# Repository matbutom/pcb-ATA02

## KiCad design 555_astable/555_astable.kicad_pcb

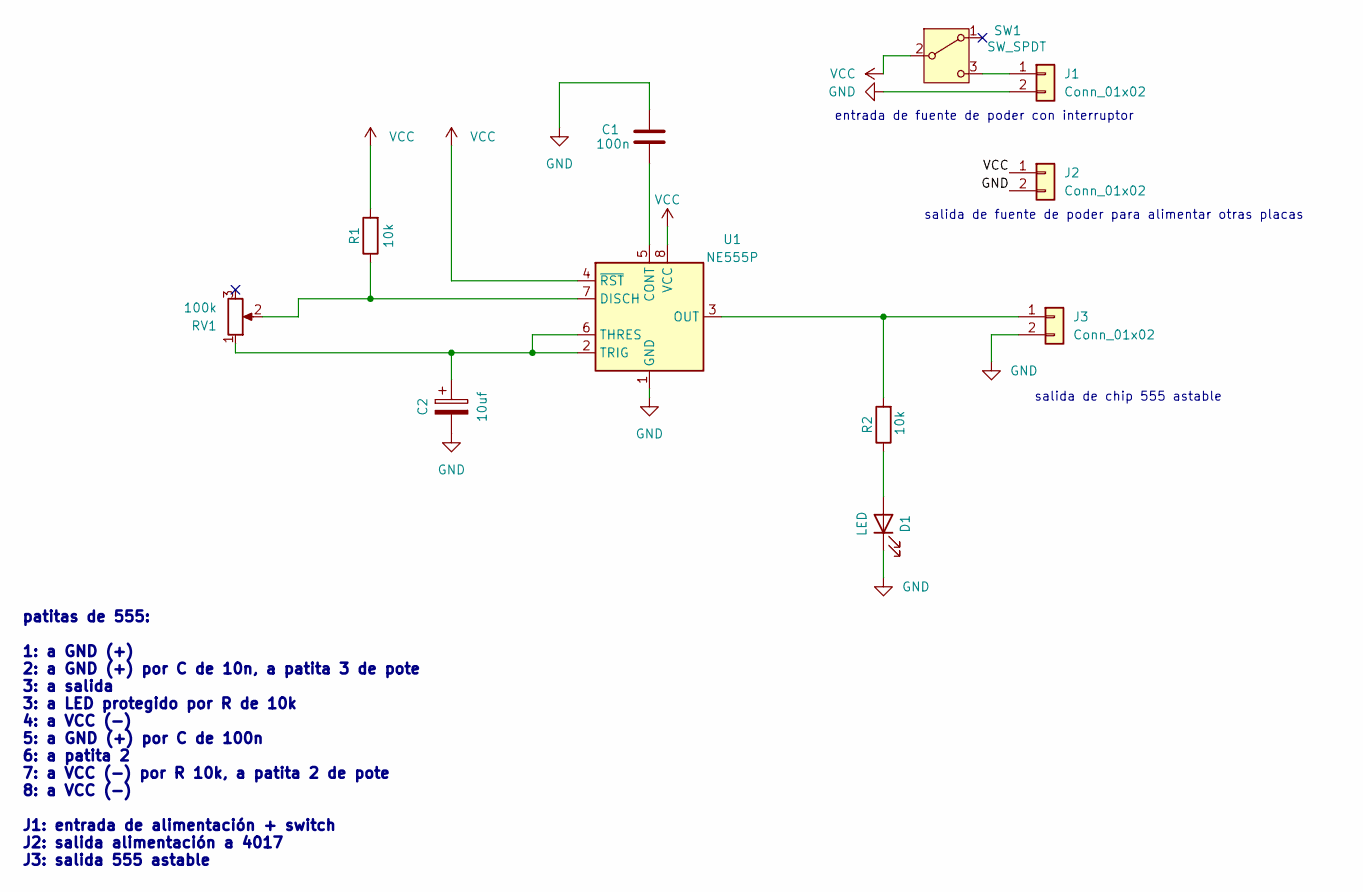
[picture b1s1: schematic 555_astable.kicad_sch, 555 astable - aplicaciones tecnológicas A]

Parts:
C1: 100n; C_Disc_D5.0mm_W2.5mm_P5.00mm
C2: 10uf; CP_Radial_D5.0mm_P2.50mm
D1: LED; LED_D5.0mm
J1, J2, J3: Conn_01x02; TerminalBlock_MaiXu_MX126-5.0-02P_1x02_P5.00mm
R1, R2: 10k; R_Axial_DIN0207_L6.3mm_D2.5mm_P10.16mm_Horizontal
RV1: 100k; TerminalBlock_MaiXu_MX126-5.0-02P_1x02_P5.00mm
SW1: SW_SPDT; spdt_ssd12d00g3
U1: NE555P; DIP-8_W7.62mm_Socket

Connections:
GND: C1.1, C2.2, D1.1 (K), J1.2, J2.2, J3.2, U1.1 (GND)
unnamed: D1.2 (A), R2.1
unnamed: J1.1, SW1.3 (C)
unnamed: J3.1, R2.2, U1.3 (OUT)
unnamed: C1.2, U1.5 (CONT)
unnamed: R1.1, RV1.2, U1.7 (DISCH)
unnamed: C2.1, RV1.1, U1.2 (TRIG), U1.6 (THRES)
VCC: J2.1, R1.2, SW1.2 (B), U1.4 (~RST), U1.8 (VCC)

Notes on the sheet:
salida de fuente de poder para alimentar otras placas
salida de chip 555 astable
patitas de 555: 1: a GND (+) 2: a GND (+) por C de 10n, a patita 3 de pote 3: a salida 3: a LED protegido por R de 10k 4: a VCC (-) 5: a GND (+) por C de 100n 6: a patita 2 7: a VCC (-) por R 10k, a patita 2 de pote 8: a VCC (-) J1: entrada de alimentación + switch J2: salida alimentación a 4017 J3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
entrada de fuente de poder con interruptor

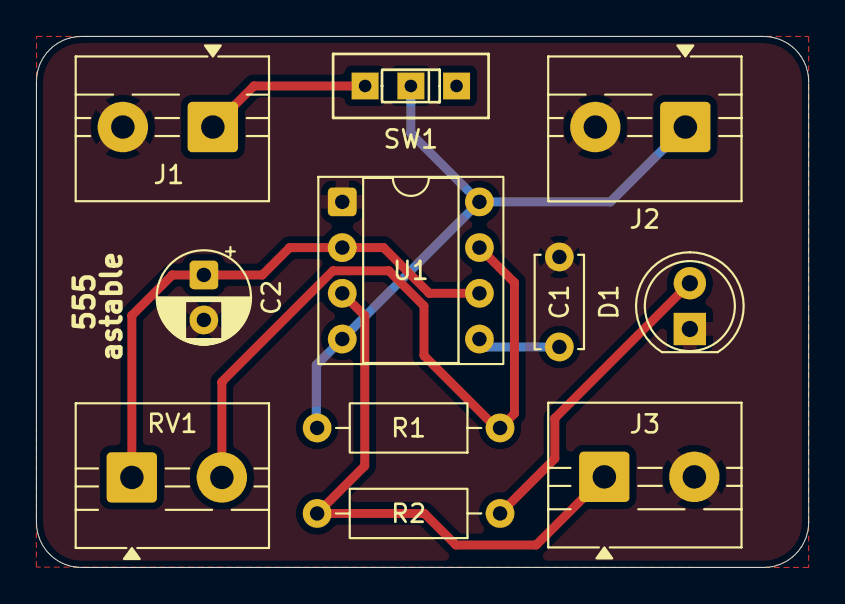
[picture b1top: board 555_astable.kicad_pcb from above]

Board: 2 copper layers, 42.9 x 29.5 mm, 11 parts (0 on the bottom side), 8 nets.

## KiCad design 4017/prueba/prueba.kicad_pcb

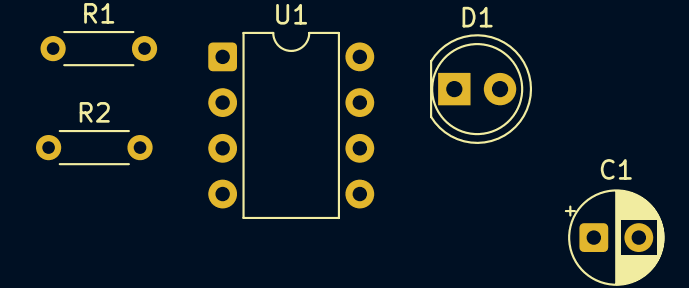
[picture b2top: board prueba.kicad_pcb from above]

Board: 2 copper layers, 5 parts (0 on the bottom side), 7 nets, no tracks yet.

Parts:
C1: C_Polarized; CP_Radial_D5.0mm_P2.50mm
D1: LED; LED_D5.0mm
R1: 10k; R_Axial_DIN0204_L3.6mm_D1.6mm_P5.08mm_Horizontal
R2: R; R_Axial_DIN0204_L3.6mm_D1.6mm_P5.08mm_Horizontal
U1: NA555P; DIP-8_W7.62mm

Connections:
GND: C1.2, D1.1 (K), U1.1 (GND)
unnamed: D1.2 (A), R2.2
unnamed: C1.1, U1.5 (CONT)
unnamed: R1.2, U1.7 (DISCH)
unnamed: R2.1, U1.3 (OUT)
unnamed: U1.2 (TRIG), U1.6 (THRES)
VCC: R1.1, U1.4 (~RST), U1.8 (VCC)

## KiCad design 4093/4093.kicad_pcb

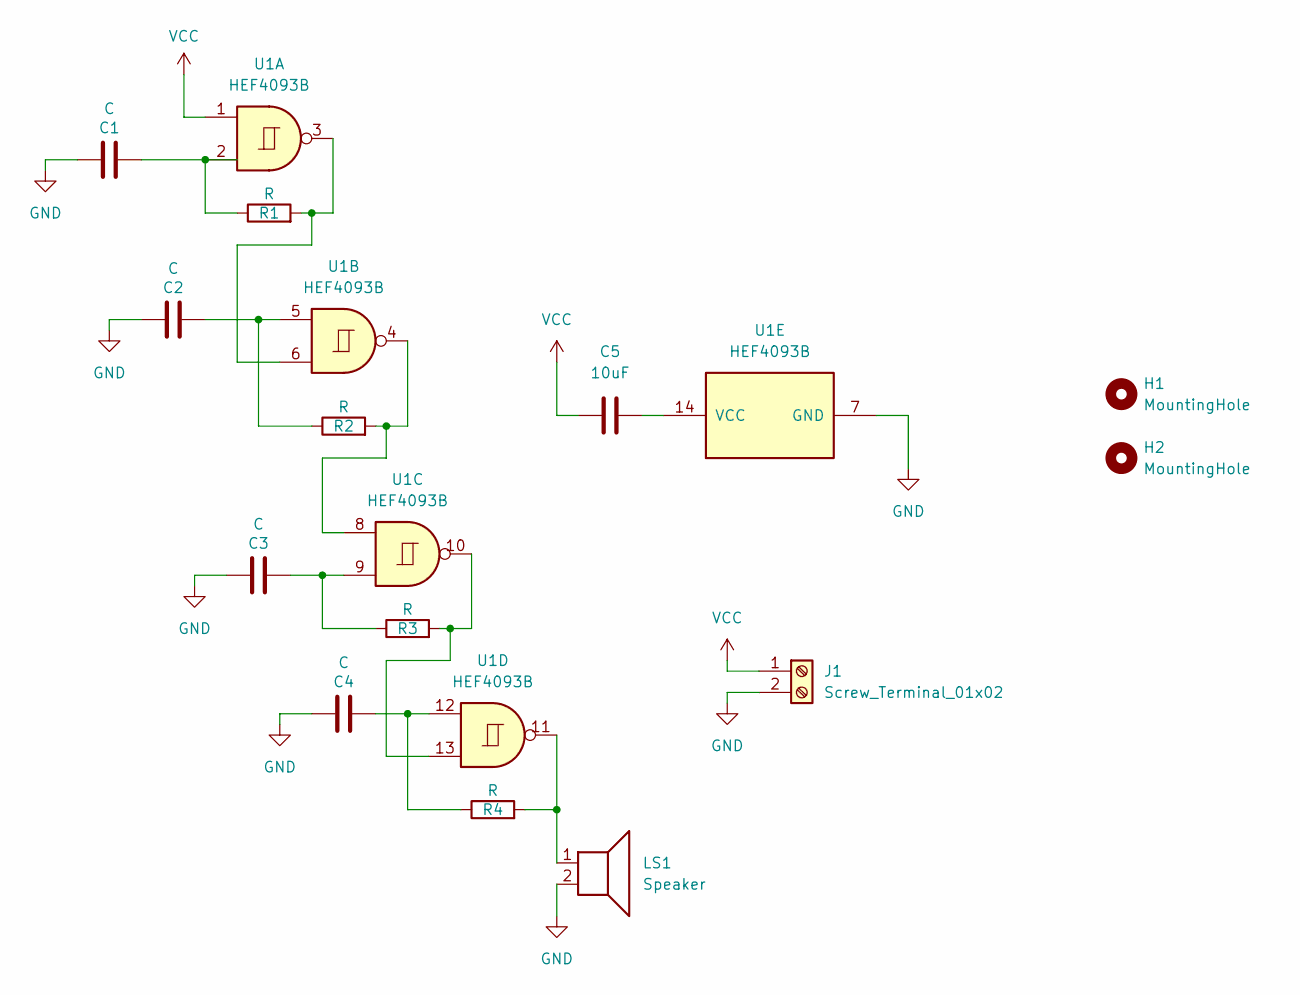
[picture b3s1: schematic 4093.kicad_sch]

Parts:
C1, C2, C3, C4: C; CP_Radial_D5.0mm_P2.00mm
C5: 10uF; CP_Radial_D5.0mm_P2.00mm
H1, H2: MountingHole; MountingHole_3.2mm_M3
J1: Screw_Terminal_01x02; TerminalBlock_MaiXu_MX126-5.0-02P_1x02_P5.00mm
LS1: Speaker; TerminalBlock_MaiXu_MX126-5.0-02P_1x02_P5.00mm
R1, R2, R3, R4: R; TerminalBlock_MaiXu_MX126-5.0-02P_1x02_P5.00mm
U1: HEF4093B; DIP-14_W7.62mm_Socket

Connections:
GND: C1.1, C2.1, C3.1, C4.1, J1.2, LS1.2, U1.7 (GND)
unnamed: C1.2, R1.1, U1.2
unnamed: C2.2, R2.1, U1.5
unnamed: C3.2, R3.1, U1.9
unnamed: C4.2, R4.1, U1.12
unnamed: LS1.1, R4.2, U1.11
unnamed: R1.2, U1.3, U1.6
unnamed: R2.2, U1.4, U1.8
unnamed: R3.2, U1.10, U1.13
unnamed: C5.2, U1.14 (VCC)
VCC: C5.1, J1.1, U1.1

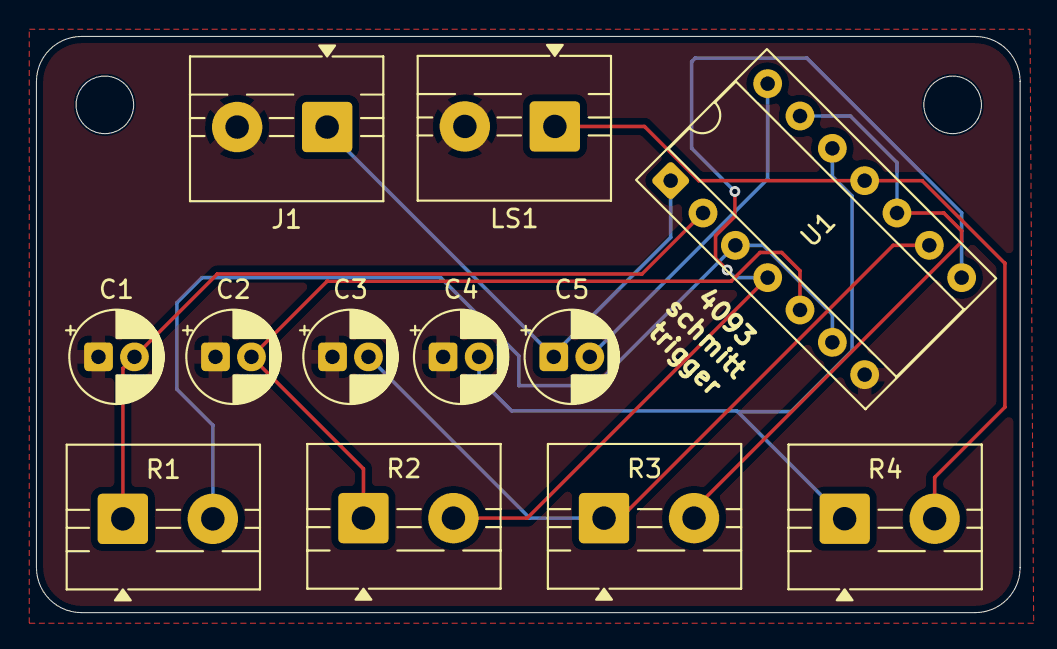
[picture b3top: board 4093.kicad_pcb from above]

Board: 2 copper layers, 54.7 x 32.0 mm, 14 parts (0 on the bottom side), 11 nets.

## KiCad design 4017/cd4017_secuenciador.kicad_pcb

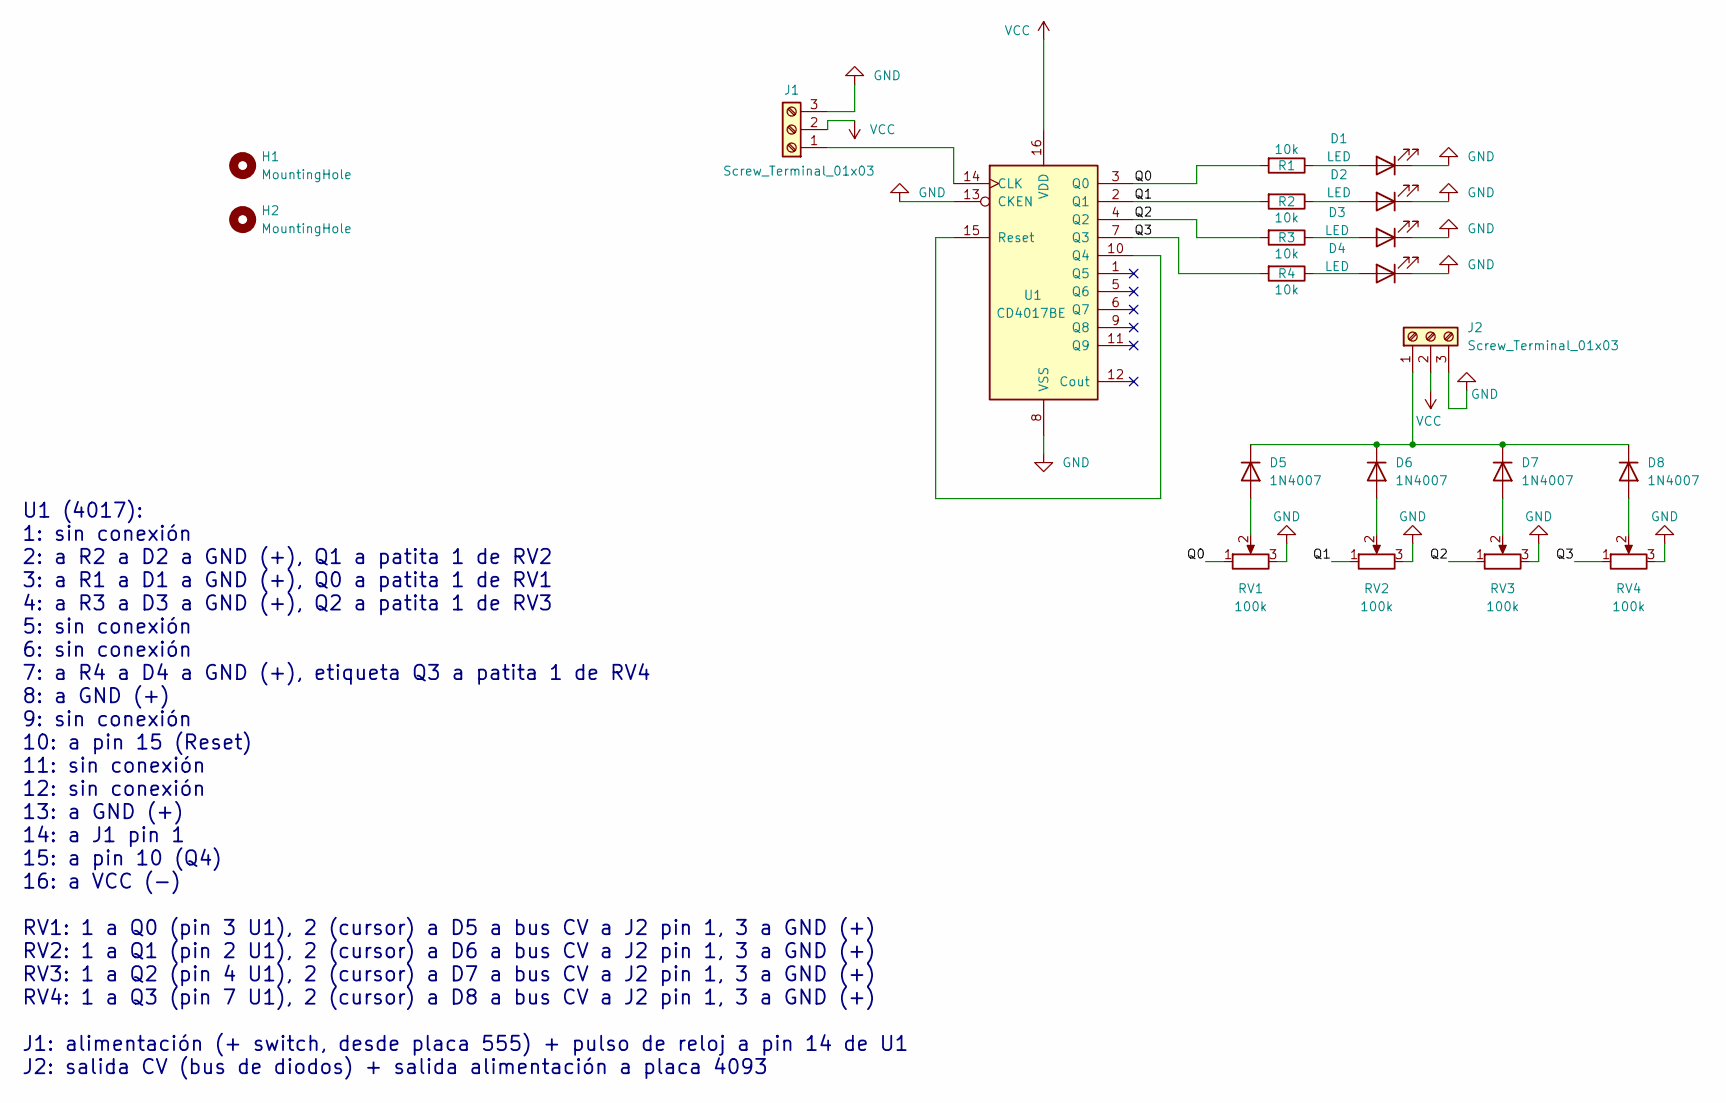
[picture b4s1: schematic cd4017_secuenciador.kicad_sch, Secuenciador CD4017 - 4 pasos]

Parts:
D1, D2, D3, D4: LED; LED_D5.0mm
D5, D6, D7, D8: 1N4007; D_DO-41_SOD81_P10.16mm_Horizontal
H1, H2: MountingHole
J1, J2: Screw_Terminal_01x03; TerminalBlock_MaiXu_MX126-5.0-03P_1x03_P5.00mm
R1, R2, R3, R4: 10k; R_Axial_DIN0207_L6.3mm_D2.5mm_P10.16mm_Horizontal
RV1, RV2, RV3, RV4: 100k; TerminalBlock_MaiXu_MX126-5.0-03P_1x03_P5.00mm
U1: CD4017BE; DIP-16_W7.62mm_Socket

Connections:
/Q0: R1.2, RV1.1, U1.3 (Q0)
/Q1: R2.2, RV2.1, U1.2 (Q1)
/Q2: R3.2, RV3.1, U1.4 (Q2)
/Q3: R4.2, RV4.1, U1.7 (Q3)
GND: D1.1 (K), D2.1 (K), D3.1 (K), D4.1 (K), J1.3, J2.3, RV1.3, RV2.3, RV3.3, RV4.3, U1.8 (VSS), U1.13 (CKEN)
unnamed: D1.2 (A), R1.1
unnamed: D2.2 (A), R2.1
unnamed: D3.2 (A), R3.1
unnamed: D4.2 (A), R4.1
unnamed: D5.2 (A), RV1.2
unnamed: D5.1 (K), D6.1 (K), D7.1 (K), D8.1 (K), J2.1
unnamed: D6.2 (A), RV2.2
unnamed: D7.2 (A), RV3.2
unnamed: D8.2 (A), RV4.2
unnamed: J1.1, U1.14 (CLK)
unnamed: U1.10 (Q4), U1.15 (Reset)
VCC: J1.2, J2.2, U1.16 (VDD)

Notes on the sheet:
U1 (4017): 1: sin conexión 2: a R2 a D2 a GND (+), Q1 a patita 1 de RV2 3: a R1 a D1 a GND (+), Q0 a patita 1 de RV1 4: a R3 a D3 a GND (+), Q2 a patita 1 de RV3 5: sin conexión 6: sin conexión 7: a R4 a D4 a GND (+), etiqueta Q3 a patita 1 de RV4 8: a GND (+) 9: sin conexión 10: a pin 15 (Reset) 1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

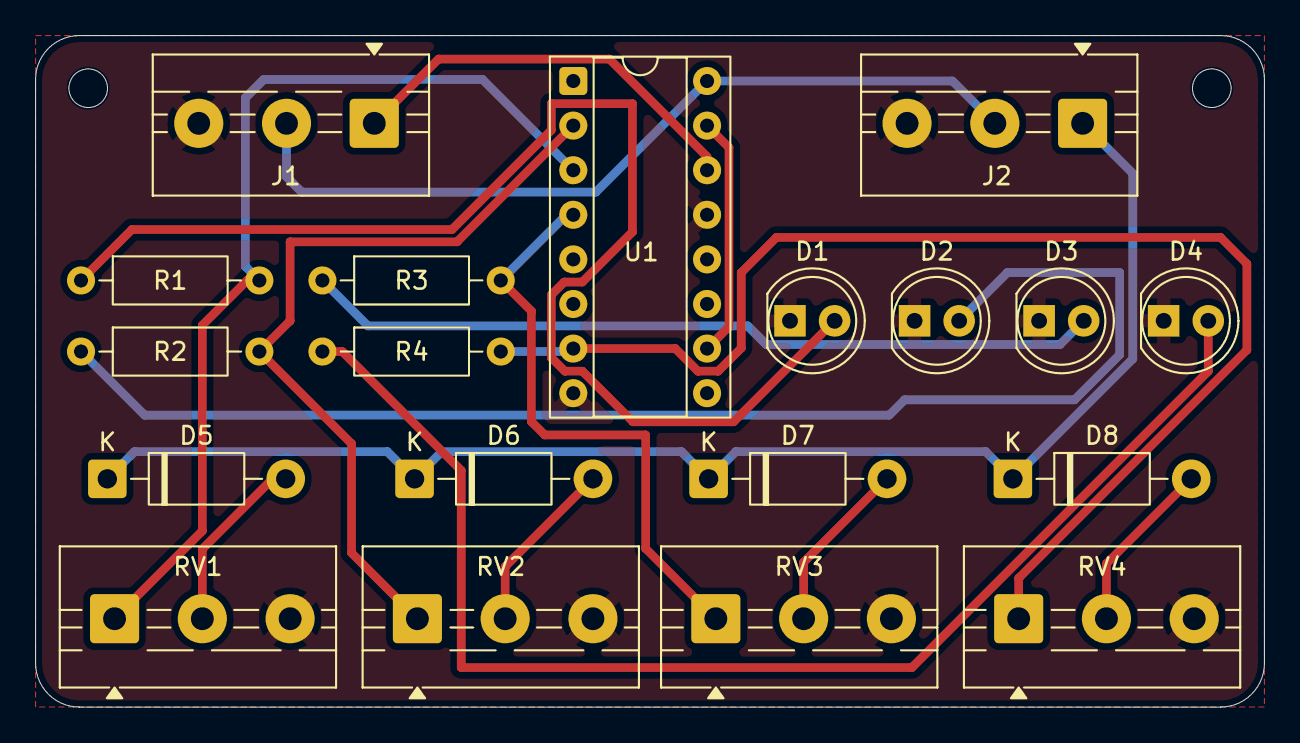
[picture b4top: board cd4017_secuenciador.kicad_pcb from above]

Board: 2 copper layers, 70.0 x 38.2 mm, 19 parts (0 on the bottom side), 17 nets.

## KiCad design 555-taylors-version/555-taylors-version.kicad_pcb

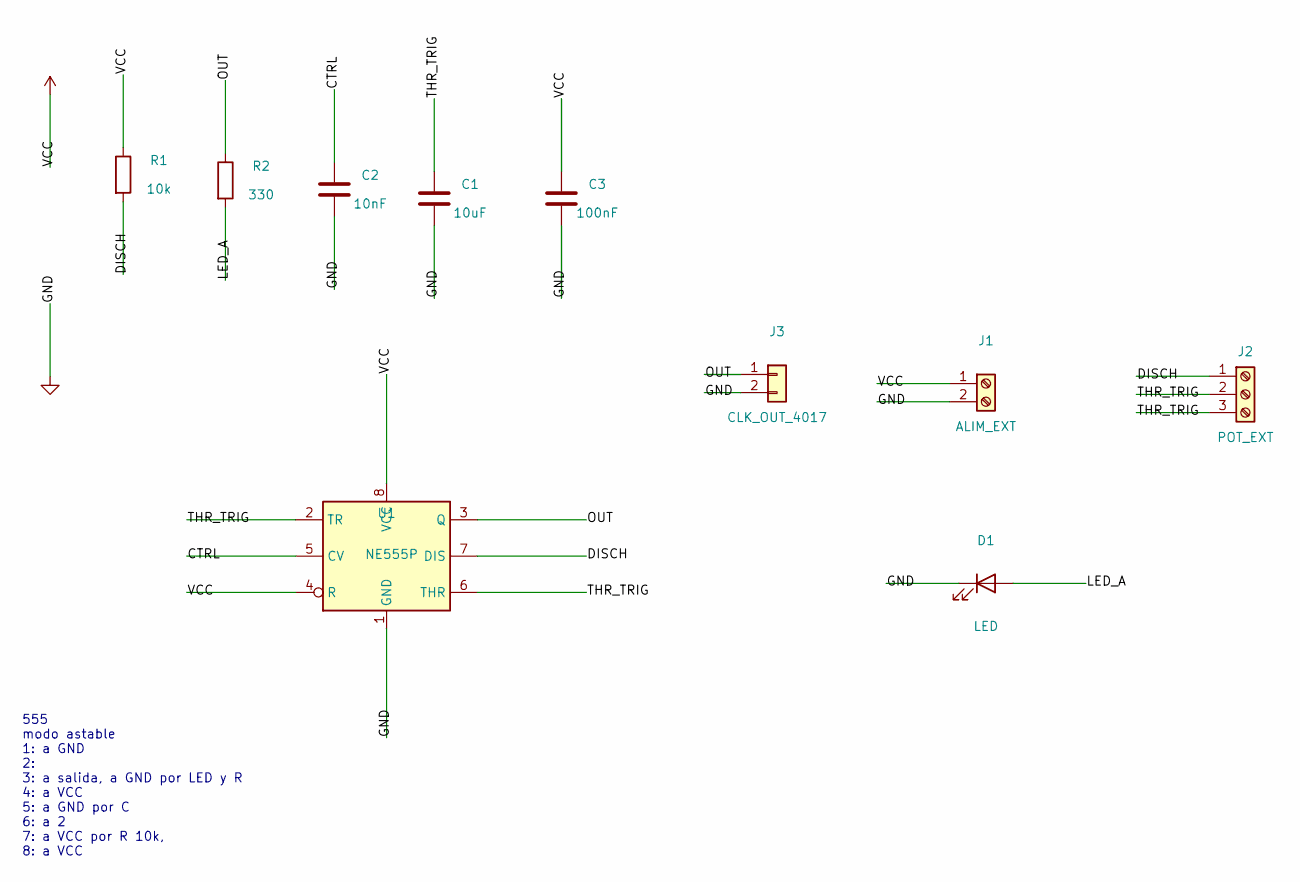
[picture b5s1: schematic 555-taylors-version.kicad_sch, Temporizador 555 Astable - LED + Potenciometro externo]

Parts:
C1: 10uF; CP_Radial_D5.0mm_P2.50mm
C2: 10nF; C_Disc_D3.0mm_W1.6mm_P2.50mm
C3: 100nF; C_Disc_D3.0mm_W1.6mm_P2.50mm
D1: LED; LED_D5.0mm
J1: ALIM_EXT; TerminalBlock_bornier-2_P5.08mm
J2: POT_EXT; TerminalBlock_bornier-3_P5.08mm
J3: CLK_OUT_4017; PinHeader_1x02_P2.54mm_Vertical
R1: 10k; R_Axial_DIN0207_L6.3mm_D2.5mm_P10.16mm_Horizontal
R2: 330; R_Axial_DIN0207_L6.3mm_D2.5mm_P10.16mm_Horizontal
U1: NE555P; DIP-8_W7.62mm_Socket

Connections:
CTRL: C2.1, U1.5 (CV)
DISCH: J2.1, R1.2, U1.7 (DIS)
GND: C1.2, C2.2, C3.2, D1.1 (K), J1.2, J3.2, U1.1 (GND)
LED_A: D1.2 (A), R2.2
OUT: J3.1, R2.1, U1.3 (Q)
THR_TRIG: C1.1, J2.2, J2.3, U1.2 (TR), U1.6 (THR)
VCC: C3.1, J1.1, R1.1, U1.4 (R), U1.8 (VCC)

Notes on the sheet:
555 modo astable 1: a GND 2: 3: a salida, a GND por LED y R 4: a VCC 5: a GND por C 6: a 2 7: a VCC por R 10k, 8: a VCC

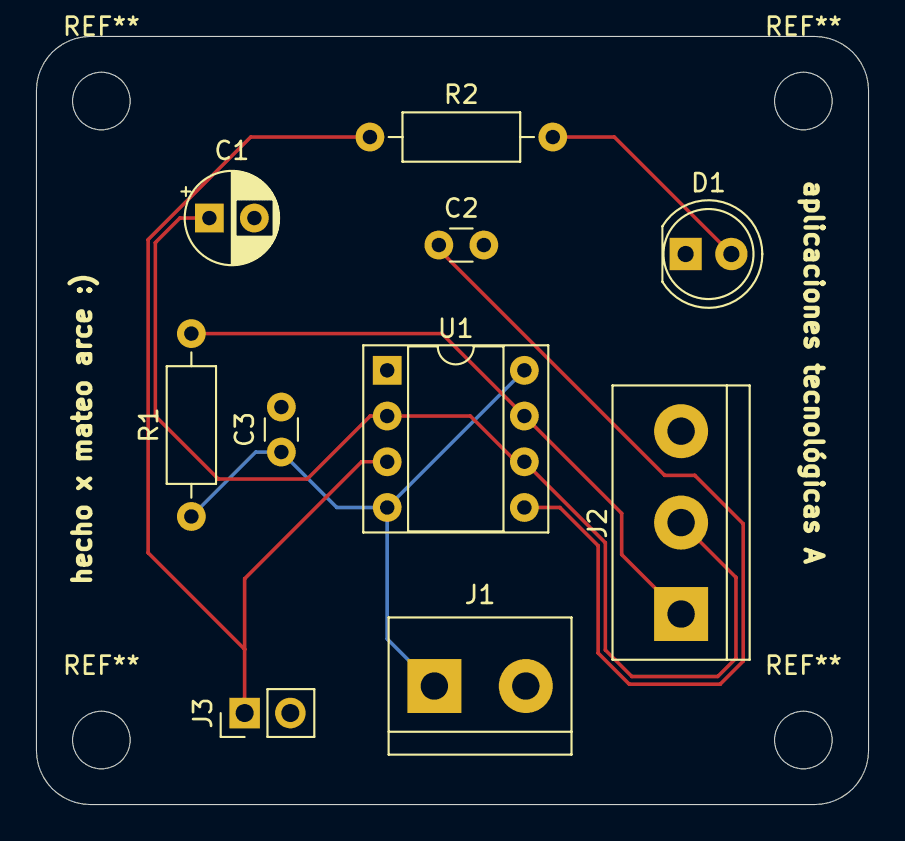
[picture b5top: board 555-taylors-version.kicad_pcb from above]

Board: 2 copper layers, 46.2 x 42.7 mm, 10 parts (0 on the bottom side), 7 nets.
